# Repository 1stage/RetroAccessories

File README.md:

# RetroAccessories
**Add-ons and accessories for retro computers by GaMon Electronics**

In Summer of 2024, GaMon approached me with the task of turning their concept sketches into CAD files that others could enjoy and use. As we had several shared interests, I agreed and began the process of "digitizing" their content.

I'll keep you updated as to my progress...

- Sean Harrington

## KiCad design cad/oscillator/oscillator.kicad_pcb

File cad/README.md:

# CAD Files
This folder contains the project files for each project that has been drafted into KiCAD.

These projects use [KiCAD Version 8](https://www.kicad.org/).

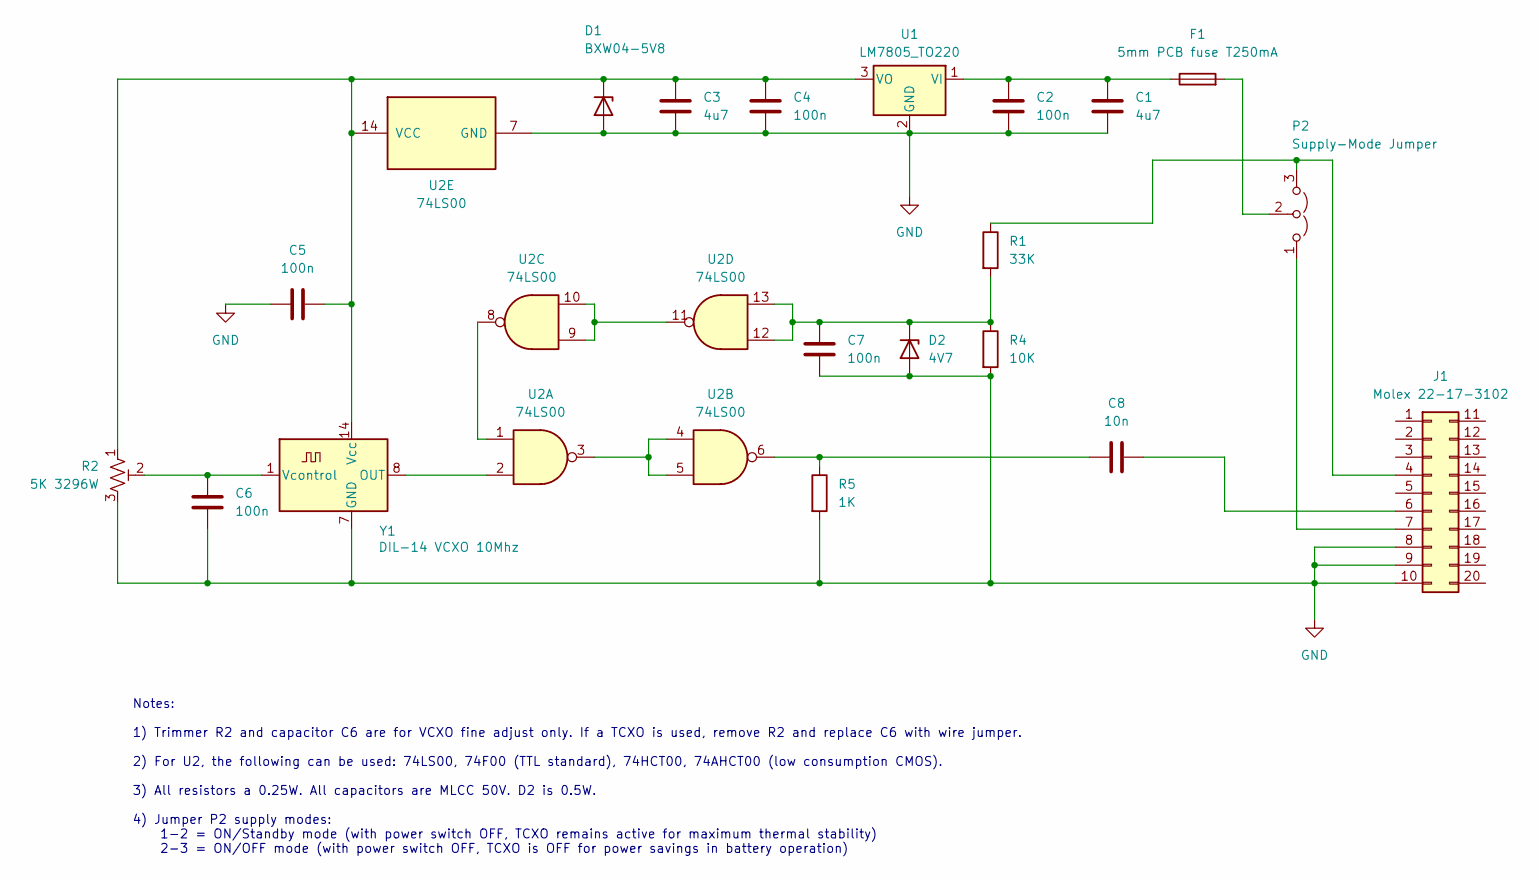
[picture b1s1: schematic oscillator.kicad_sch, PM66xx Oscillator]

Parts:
C1, C3: 4u7; C_Axial_L3.8mm_D2.6mm_P10.00mm_Horizontal
C2, C4, C5, C6, C7: 100n; C_Axial_L3.8mm_D2.6mm_P10.00mm_Horizontal
C8: 10n; C_Axial_L3.8mm_D2.6mm_P10.00mm_Horizontal
D1: BXW04-5V8; D_A-405_P10.16mm_Horizontal
D2: 4V7; D_A-405_P10.16mm_Horizontal
F1: 5mm PCB fuse T250mA; Fuse_Littelfuse_372_D8.50mm
J1: Molex 22-17-3102; PinHeader_2x10_P2.54mm_Vertical
P2: Supply-Mode Jumper; PinSocket_1x03_P2.54mm_Vertical
R1: 33K; R_Axial_DIN0207_L6.3mm_D2.5mm_P10.16mm_Horizontal
R2: 5K 3296W; Potentiometer_Bourns_3296W_Vertical
R4: 10K; R_Axial_DIN0207_L6.3mm_D2.5mm_P10.16mm_Horizontal
R5: 1K; R_Axial_DIN0207_L6.3mm_D2.5mm_P10.16mm_Horizontal
U1: LM7805_TO220; TO-220-3_Horizontal_TabDown
U2: 74LS00; CERDIP-14_W7.62mm_SideBrazed
Y1: DIL-14 VCXO 10Mhz; Oscillator_DIP-14

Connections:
GND: C1.2, C2.2, C3.2, C4.2, C5.1, C6.2, C7.2, D1.2 (A), D2.2 (A), J1.8, J1.9, J1.10, R2.3, R4.2, R5.2, U1.2 (GND), U2.7 (GND), Y1.7 (GND)
unnamed: C8.1, R5.1, U2.6
unnamed: C3.1, C4.1, C5.2, D1.1 (K), R2.1, U1.3 (VO), U2.14 (VCC), Y1.14 (Vcc)
unnamed: C7.1, D2.1 (K), R1.2, R4.1, U2.12, U2.13
unnamed: J1.4, P2.3 (B), R1.1
unnamed: C8.2, J1.6
unnamed: J1.7, P2.1 (A)
unnamed: F1.2, P2.2 (C)
unnamed: C1.1, C2.1, F1.1, U1.1 (VI)
unnamed: U2.1, U2.8
unnamed: U2.3, U2.4, U2.5
unnamed: U2.9, U2.10, U2.11
unnamed: U2.2, Y1.8 (OUT)
unnamed: C6.1, R2.2, Y1.1 (Vcontrol)

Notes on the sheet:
Notes: 1) Trimmer R2 and capacitor C6 are for VCXO fine adjust only. If a TCXO is used, remove R2 and replace C6 with wire jumper. 2) For U2, the following can be used: 74LS00, 74F00 (TTL standard), 74HCT00, 74AHCT00 (low consumption CMOS). 3) All resistors a 0.25W. All capacitors are MLCC 50V. D2 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

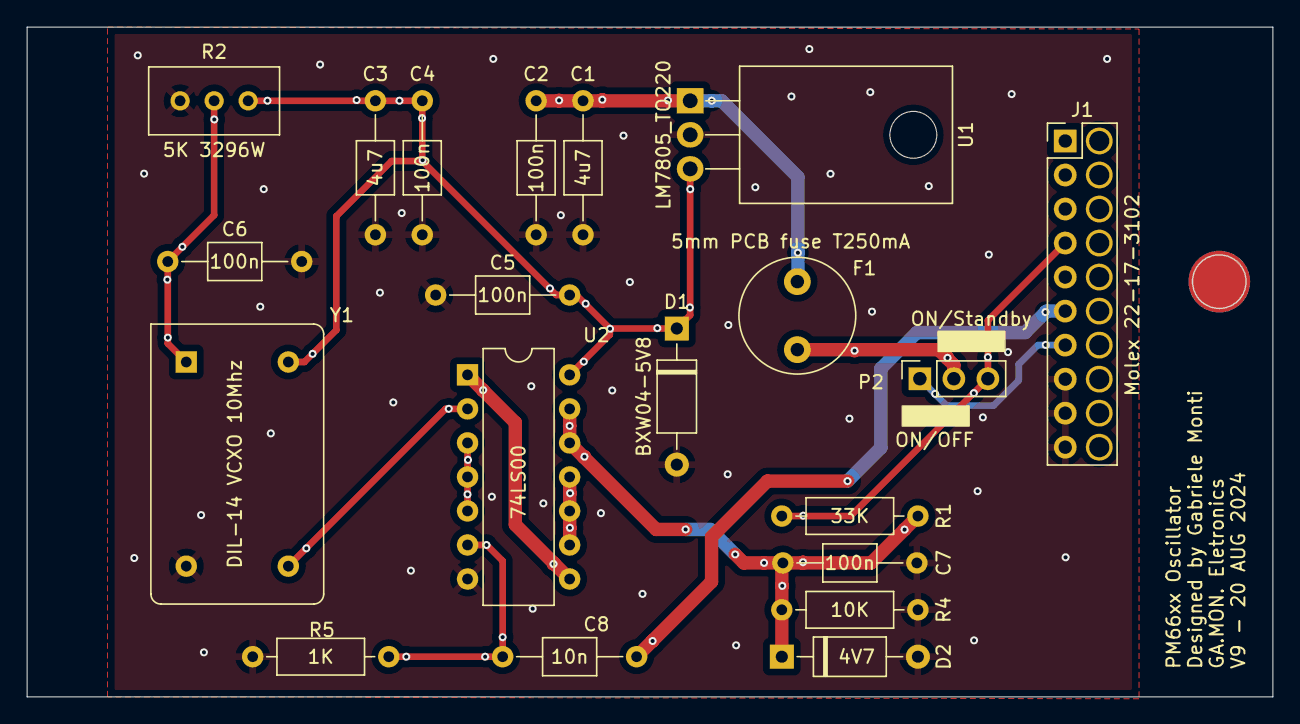
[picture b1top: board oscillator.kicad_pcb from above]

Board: 2 copper layers, 93.0 x 50.0 mm, 20 parts (0 on the bottom side), 14 nets.

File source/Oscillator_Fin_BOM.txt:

Philips PM66xx Oscillator BOM:

_ R1 : Axial 33Kohm 1/4W (reduce to 27Kohm if output have difficulties to resume from standby)
_ R2 : 5Kohm vertical 10 turns trimmer (Bourns 3296W or similar)
_ R4 : Axial 10Kohm 1/4W
_ R5 : Axial 1Kohm 1/4W

_ C1 : 100nF 50V MLCC
_ C2 : 4.7uF 25V Tantalum (or MLCC)
_ C3 : 4.7uF 25V Tantalum (or MLCC)
_ C4 : 100nF 50V MLCC
_ C5 : 100nF 50V MLCC
_ C6 : 100nF 50V MLCC
_ C7 : 100nF 50V MLCC
_ C8 : 10nF 50V MLCC

_ D1 : BZW04-5V8 (or equivalent unidirectional 5.8V TVS diode)
_ D2 : 1N5230 (or equivalent 4.7V 0.5W Zener diode)

_ U1 : LM7805 or uA7805 or KA7805 (TO-220 case)
_ U2 : 74LS00 or 74HCT00 or 74F00 or 74AHCT00 (NO 74HC00 or 74C00)

_ Y1 : 10Mhz VCXO or TCXO in DIL-14 case

_ F1 : T250mA 5mm THT Fuse

_ J1 : MOLEX 22-17-3102 (10pin 2.54mm female connector)

_ P2 : 3pin 2.54mm male pin-strip

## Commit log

2024-08-19 Setting up
2024-08-19 Add files via upload
    This little project is intended for all the owners of Philips "PM66xx" family Frequency Meters and Counters, who need to upgrade or replace one of the following time-base oscillators fitted in those 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
    _ PM9677
    _ PM9678
    _ PM9679
    _ PM9690
    This new PCB respects the original module's connections, dimensions, and mechanical fastening, to garantee a direct replacement without modifications.
2024-08-19 Create test
2024-08-19 Oscillator Folder
2024-08-20 Started Oscillator CAD Test
2024-08-20 Oscillator Updates
2024-08-20 Oscillator V9 Updates
2024-08-21 README.md
